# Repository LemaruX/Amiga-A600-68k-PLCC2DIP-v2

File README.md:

# Amiga-A600-68k-PLCC2DIP-v2
 This is a simple adaptor to allow the use of 64pin DIP CPU's and accelerators on an Amiga 600. This has been re-worked from the v1 design, with the DIP socket rotated 180 degrees, and a smaller footprint that maybe better suited for smaller accelerators or CPUs (a TF536 can still be used, but the socket needs to be mounted a certain way, see details below)

**PLEASE NOTE** This design has not currently been tested for fit with the TF536. I am currently waiting on my boards to be delivered to test them. It should otherwise be fine for use as uses the same schematic as the previous version. 

---

## Summary
This is a basic adaptor that disables the on-board 68000 on an Amiga 600, and provides a 64pin DIP socket to allow you to connect a 64pin CPU or an A500 accelerator card. It is based on an idea by [Kludge](https://gitlab.com/kludge) and a modified version of his [Ice Scraper](https://gitlab.com/kludge/a600-ice-scraper) breakout board. 

**Rev B Update** - The board has now been updated to a 4-layer design. It also includes a floppy power connector to provide additional power. **DO NOT use this connector for powering any devices, it is ONLY for providing additional power to the adaptor. ONLY apply power from the same power source that is powering the Amiga (E.g. the floppy power connector). DO NOT USE AN EXTERNAL POWER SUPPLY.** 

To date it has only been tested successfully with the devices listed below. If anyone tests the adaptor successfully on another device, then please let me know and I can update the list.

- 68010 CPU
- 68000 CPU
- Terriblefire TF536 (This requires a specific firmware to work on the A600 which you can find [here](https://www.exxoshost.co.uk/forum/viewtopic.php?f=93&t=3438))
- Matzes 68EC020TK card (Although this device is reported to work, it is too large to close the A600 case when fitted)

- PiStorm - **NOTE** The PiStorm board has been tested, however due to the stacking nature of the adaptor, PiStorm and Pi it is not an ideal fit within the case. You are better off using my PiStorm600 board instead. 

**PLEASE NOTE** If using with a Terriblefire 536 in the Amiga 600, you must use a certain revision [firmware](https://www.exxoshost.co.uk/forum/viewtopic.php?f=93&t=3438). Unfortunately due to the size of the TF536, to allow for it to fit inside the A600 and the case to be fully closed, you must solder the 64pin DIP socket (or pin strip) with the upper most row of pins higher than the bottom row. Unlike the previous version, you can do this by using a row of pin strip underneath the top row of pins on the DIP socket as shown in the images below. This allows the TF536 to sit at the correct angle so that the rear of the card sits slightly over the lip at the back of the A600 case.

Devices that have been tested and do **NOT** work are listed below. Again, please let me know when you find devices that do not work so the list can be updated. 

- Terriblefire TF534

---

## Bill Of Materials

| Ref | Value | Footprint | Notes |
| ----------- | ----------- | ----------- | ----------- |
| U1 |  | PLCC68 Socket| A good quality socket such as an Augat PCS-068A is desirable. For a better fit on the A600 CPU, please modify the socket as per the instructions [here](PLCC-Rework.md) |
| U2 |  | DIP64 Socket | |
| R1 | 220R | 0805 | |
| R2 | 1k | 0805 | |
| C1, C2, C3, C4, C5 | 10uf | 0805 | |
| J1 |  | 171826-4 | TE Connectivity floppy power header |

---

## Mounting

To achieve the best fit on the A600 CPU, please use a good quality PLCC socket with strong pins (such as the Augat PCS-068A, which is discontinued but can still be found online). As the PLCC socket is being used in a way that it is not intended, please follow the instructions [here](PLCC-Rework.md) to modify the socket. This will allow it to grip the on-board 68k better, giving a better connection and preventing it from easily popping off.

There are also two mounting holes, which can be used to attach it to the A600 motherboard using the HDD mounting holes. For this, I use M1.6 x 16mm screws pushed through from underneath the motherboard. Do not tighten the nuts up too much as this can damage either the adaptor or your motherboard. I use 3D printed spacers about 8.3mm in height to support the board (this is based on the height of the PLCC socket after it has been modified), but any spacer the correct size will suffice. I would advise measuring the height of the PLCC socket (after it has been modified accordingly) and using spacers of an equal height. 

I have included the STL files for the spacers that I use in the STL folder. To prevent the nuts coming loose, I use a small dab of nail varnish on the threads once they have been tightened as required. This prevents them from coming loose, but still allows for them to be easily removed. I have also included an STL file for a small thumbscrew part, which you can push the M1.6 nuts into before placing them on the screws. By using these, it is much easier to tighten and remove the nuts if/when required, without the use of any additional tools.

---

## License

Shield: [![CC BY-NC-SA 4.0][cc-by-nc-sa-shield]][cc-by-nc-sa]

This work is licensed under a [Creative Commons Attribution-NonCommercial-ShareAlike 4.0
International License][cc-by-nc-sa].

[![CC BY-NC-SA 4.0][cc-by-nc-sa-image]][cc-by-nc-sa]

[cc-by-nc-sa]: http://creativecommons.org/licenses/by-nc-sa/4.0/
[cc-by-nc-sa-image]: https://licensebuttons.net/l/by-nc-sa/4.0/88x31.png
[cc-by-nc-sa-shield]: https://img.shields.io/badge/License-CC%20BY--NC--SA%204.0-lightgrey.svg

---

## Thanks

- Kludge for the original idea and basic schematic
- 8 Bit Dreams and alenppc for testing the board
- [SukkoPera](https://github.com/SukkoPera) for the upside down PLCC socket as used in his excellent [A600 FastRAM expansion](https://github.com/SukkoPera/OpenAmiga600FastRamExpansion)
- Terriblefire for the TF536, which was the sole reason I made this as I wanted to stick one in my A600

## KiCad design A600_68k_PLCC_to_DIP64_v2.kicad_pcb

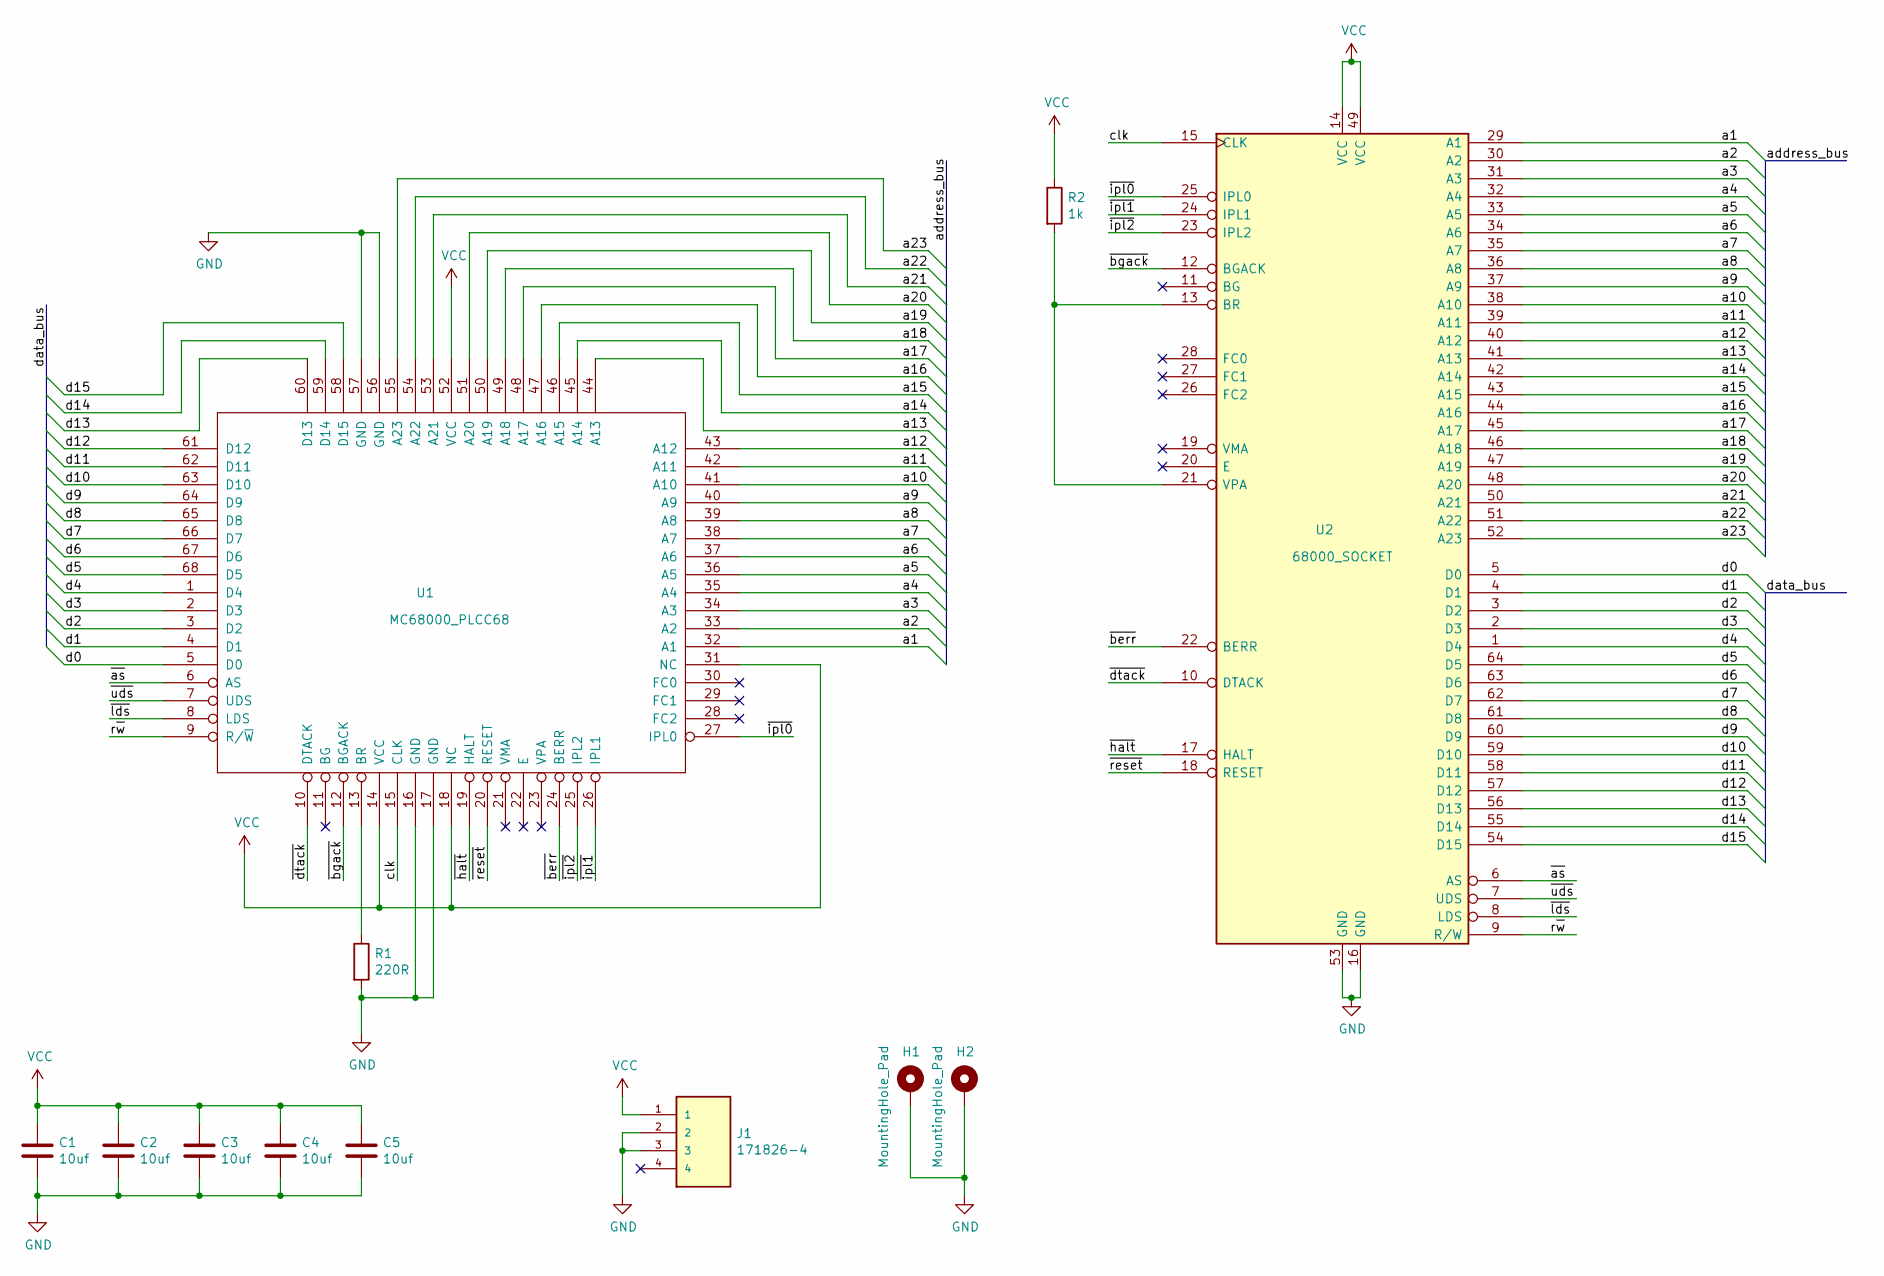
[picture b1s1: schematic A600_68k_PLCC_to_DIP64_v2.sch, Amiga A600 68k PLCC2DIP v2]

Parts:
C1, C2, C3, C4, C5: 10uf; C_0805_2012Metric_Pad1.18x1.45mm_HandSolder
H1, H2: MountingHole_Pad; MountingHole_2mm_Pad_Via
J1: 171826-4; TE_171826-4
R1: 220R; R_0805_2012Metric_Pad1.20x1.40mm_HandSolder
R2: 1k; R_0805_2012Metric_Pad1.20x1.40mm_HandSolder
U1: MC68000_PLCC68; PLCC-68_THT-SocketUpsideDown
U2: 68000_SOCKET; DIP-64_W22.86mm_Socket_ThinRoundPads_IC

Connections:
/a1: U1.32 (A1), U2.29 (A1)
/a2: U1.33 (A2), U2.30 (A2)
/a3: U1.34 (A3), U2.31 (A3)
/a4: U1.35 (A4), U2.32 (A4)
/a5: U1.36 (A5), U2.33 (A5)
/a6: U1.37 (A6), U2.34 (A6)
/a7: U1.38 (A7), U2.35 (A7)
/a8: U1.39 (A8), U2.36 (A8)
/a9: U1.40 (A9), U2.37 (A9)
/a10: U1.41 (A10), U2.38 (A10)
/a11: U1.42 (A11), U2.39 (A11)
/a12: U1.43 (A12), U2.40 (A12)
/a13: U1.44 (A13), U2.41 (A13)
/a14: U1.45 (A14), U2.42 (A14)
/a15: U1.46 (A15), U2.43 (A15)
/a16: U1.47 (A16), U2.44 (A16)
/a17: U1.48 (A17), U2.45 (A17)
/a18: U1.49 (A18), U2.46 (A18)
/a19: U1.50 (A19), U2.47 (A19)
/a20: U1.51 (A20), U2.48 (A20)
/a21: U1.53 (A21), U2.50 (A21)
/a22: U1.54 (A22), U2.51 (A22)
/a23: U1.55 (A23), U2.52 (A23)
/clk: U1.15 (CLK), U2.15 (CLK)
/d0: U1.5 (D0), U2.5 (D0)
/d1: U1.4 (D1), U2.4 (D1)
/d2: U1.3 (D2), U2.3 (D2)
/d3: U1.2 (D3), U2.2 (D3)
/d4: U1.1 (D4), U2.1 (D4)
/d5: U1.68 (D5), U2.64 (D5)
/d6: U1.67 (D6), U2.63 (D6)
/d7: U1.66 (D7), U2.62 (D7)
/d8: U1.65 (D8), U2.61 (D8)
/d9: U1.64 (D9), U2.60 (D9)
/d10: U1.63 (D10), U2.59 (D10)
/d11: U1.62 (D11), U2.58 (D11)
/d12: U1.61 (D12), U2.57 (D12)
/d13: U1.60 (D13), U2.56 (D13)
/d14: U1.59 (D14), U2.55 (D14)
/d15: U1.58 (D15), U2.54 (D15)
/r~w: U1.9 (R/~W), U2.9 (R/W)
/~as: U1.6 (AS), U2.6 (AS)
/~berr: U1.24 (BERR), U2.22 (BERR)
/~bgack: U1.12 (BGACK), U2.12 (BGACK)
/~dtack: U1.10 (DTACK), U2.10 (DTACK)
/~halt: U1.19 (HALT), U2.17 (HALT)
/~ipl0: U1.27 (IPL0), U2.25 (IPL0)
/~ipl1: U1.26 (IPL1), U2.24 (IPL1)
/~ipl2: U1.25 (IPL2), U2.23 (IPL2)
/~lds: U1.8 (LDS), U2.8 (LDS)
/~reset: U1.20 (RESET), U2.18 (RESET)
/~uds: U1.7 (UDS), U2.7 (UDS)
GND: C1.2, C2.2, C3.2, C4.2, C5.2, H1.1, H2.1, J1.2, J1.3, R1.2, U1.16 (GND), U1.17 (GND), U1.56 (GND), U1.57 (GND), U2.16 (GND), U2.53 (GND)
unnamed: R1.1, U1.13 (BR)
unnamed: R2.2, U2.13 (BR), U2.21 (VPA)
VCC: C1.1, C2.1, C3.1, C4.1, C5.1, J1.1, R2.1, U1.14 (VCC), U1.18 (NC), U1.31 (NC), U1.52 (VCC), U2.14 (VCC), U2.49 (VCC)

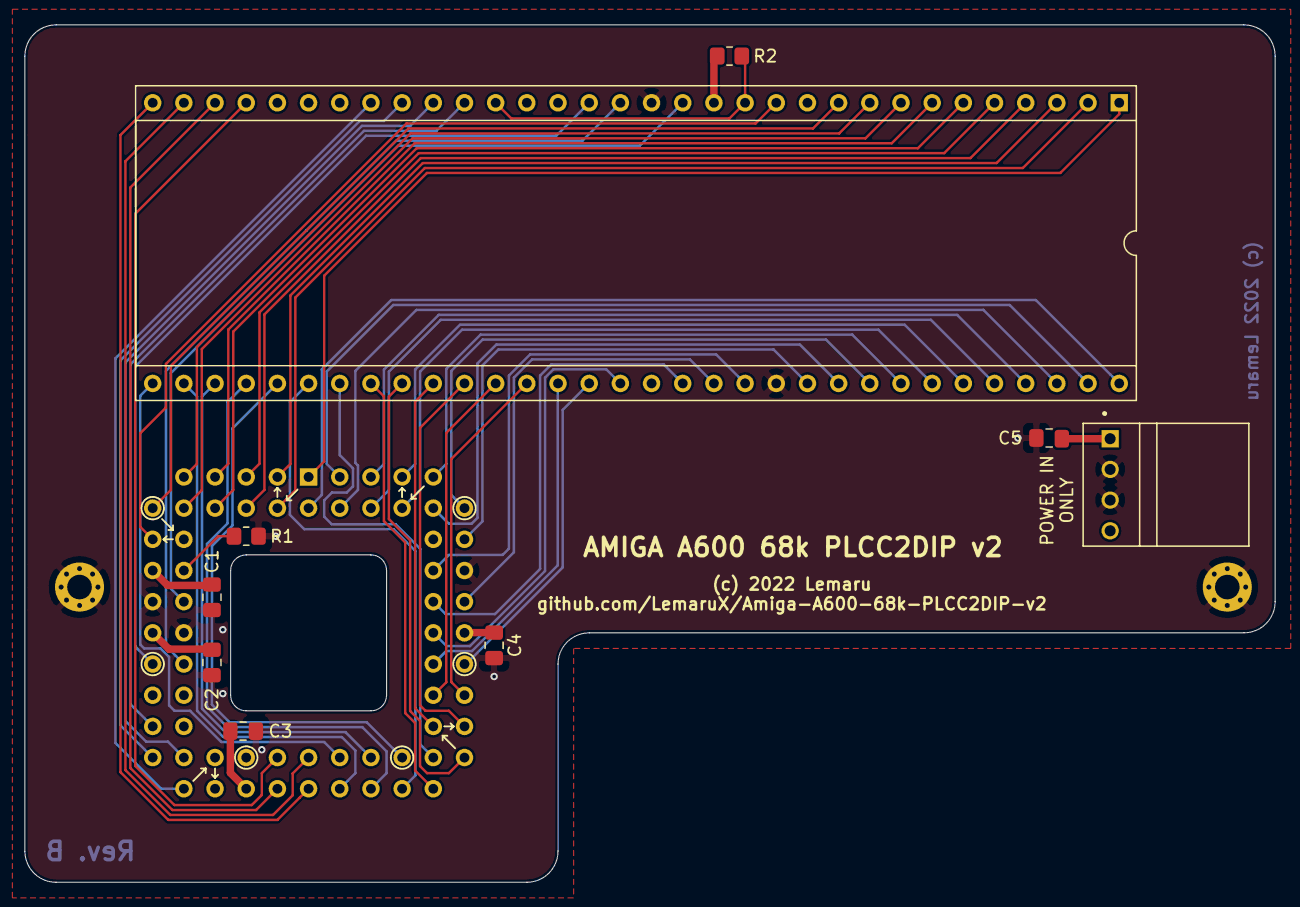
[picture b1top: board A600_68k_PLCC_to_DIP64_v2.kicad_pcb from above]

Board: 4 copper layers, 101.9 x 69.8 mm, 12 parts (0 on the bottom side), 56 nets.

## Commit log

2020-12-02 Added files & updated readme
2021-07-15 updated VCC handling
    updated PLCC nets to have extra VCC lines from N/C pins to better support thirsty cards like PiStorm.
2021-07-15 Updated readme & tweaked a trace
2022-01-03 Updated to Rev B
    Re-routed 4-layer design.
2022-01-03 Tweaked silk screen and updated gerbers
2022-03-01 Added GND vias, and corrected cap values

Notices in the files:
A600_68k_PLCC_to_DIP64_v2.kicad_pcb:
(c) 2022 Lemaru
